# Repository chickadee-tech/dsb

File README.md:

# Chickadee Tech Dual Serial Breakout Polystack Mod #
This mod breakouts out two UARTs for any use. It includes 3.3v to 5v logic level shifting so ensure that all things connected are 5v tolerant.

## Documentation ##
See the [wiki](https://github.com/chickadee-tech/dsb/wiki) for documentation.

## Polystack ##
This **mod** board is part of the Polystack platform for modular microcontrol systems. More information on the platform can be found at [polystack.org](http://polystack.org).

## Support ##
If you need support with a board you own or have development questions please email support@chickadee.tech or check [chickadee.tech/support](https://chickadee.tech/support) for other ways to get support.

## Contributing ##
Please note that this project is released with a [Contributor Code of Conduct](CODE_OF_CONDUCT.md). By participating in this project you agree to abide by its terms.

### Setup ###
Components and footprints for PCB parts are not included in this repository. Instead, checkout the [chickadee-tech/kicad-libs](https://github.com/chickadee-tech/kicad-libs) repository in the same directory that this repository is checked out in. All part definitions should be relative so that they will load correctly.

### Pull requests ###
For fixes please submit a pull request to the original repository. After the pull request is merged, check the [Chickadee Tech Active Contributor Discount (ACD)](https://chickadee.tech/active-contributor) to see if you are eligible for a discount code to use on your next purchase.

### Derivatives ###
If developing your own version of the Dual Serial Breakout board please remove all Chickadee Tech trademarks and follow the [CC-BY license](LICENSE). While not required, please consider open sourcing your modifications so others can learn from your improvements. If you do email support@chickadee.tech and we may choose to add your project to the ACD.

You may also license the Polystack logo for free by emailing support@chickadee.tech. We'll ask for your gerbers to ensure the design complies with specifications laid out [here](https://github.com/chickadee-tech/polystack/wiki) and provide written permission to use the trademark after compliance has been demonstrated.

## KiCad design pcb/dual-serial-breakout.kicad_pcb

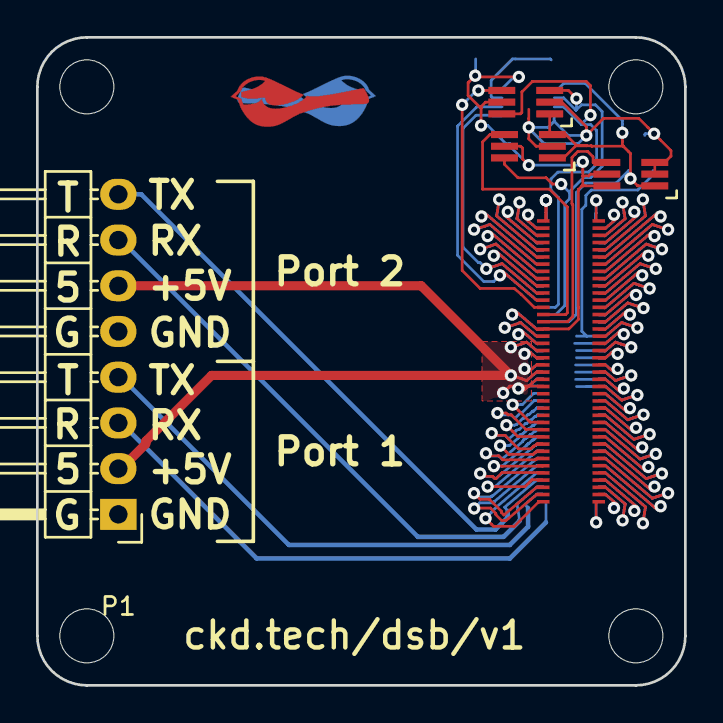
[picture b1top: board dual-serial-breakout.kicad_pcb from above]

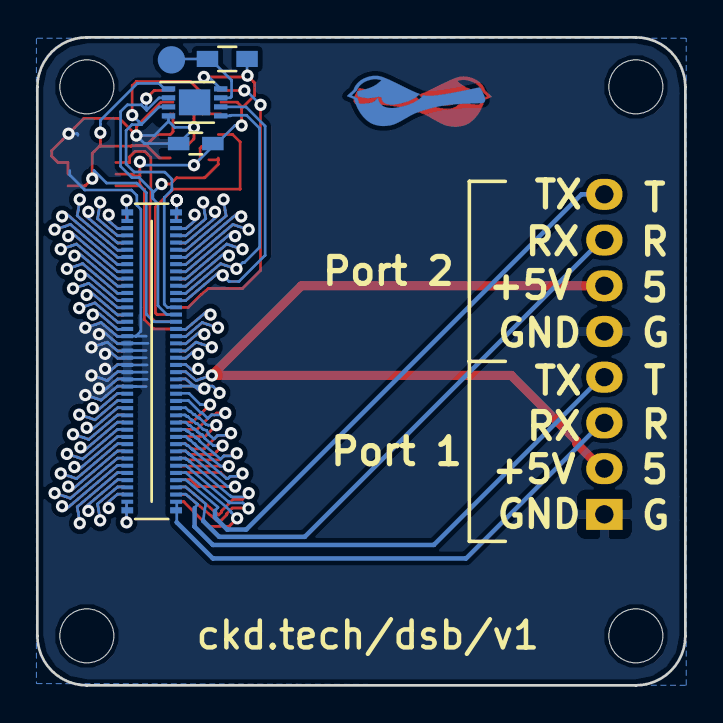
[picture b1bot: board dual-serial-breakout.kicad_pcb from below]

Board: 2 copper layers, 36.0 x 36.0 mm, 10 parts (5 on the bottom side), 72 nets.

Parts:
P1: CONN_01X08; Pin_Header_Angled_1x08
PORT_ANDOR1: SN74LVC1G0832; SC-70-6_Handsoldering
PORT_C1: 0.1uF; C_0603_HandSoldering
PORT_IC1: AT24CS02-MAHM; DFN-8-1EP_3x2mm_Pitch0.5mm
PORT_IN1: CKD_SANDWICH; DF40-80pin-Header
PORT_INV1: SN74LVC1G58; SC-70-6_Handsoldering
PORT_OUT1: CKD_SANDWICH; DF40-3-4mm-80pin-Receptacle
PORT_P1: CONN_01X01; Measurement_Point_Round-SMD-Pad_Small
PORT_R1: 10k; R_0603_HandSoldering
PORT_XOR1: SN74LVC1G58; SC-70-6_Handsoldering

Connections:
+5V: P1.2, P1.6, PORT_IN1.19, PORT_IN1.20, PORT_IN1.21, PORT_IN1.22, PORT_IN1.23, PORT_IN1.24, PORT_OUT1.19, PORT_OUT1.20, PORT_OUT1.21, PORT_OUT1.22, PORT_OUT1.23, PORT_OUT1.24
/ExpansionPort/3V3_0.3A_E: PORT_IN1.17, PORT_OUT1.17
/ExpansionPort/3V3_0.3A_LL: PORT_ANDOR1.5, PORT_C1.1, PORT_IC1.8, PORT_IN1.16, PORT_INV1.5, PORT_INV1.6, PORT_OUT1.16, PORT_R1.2, PORT_XOR1.5
/ExpansionPort/+BATT: PORT_IN1.18, PORT_OUT1.18
/ExpansionPort/ADC1: PORT_IN1.49, PORT_OUT1.49
/ExpansionPort/ADC2: PORT_IN1.50, PORT_OUT1.50
/ExpansionPort/GPIO1: PORT_IN1.5, PORT_OUT1.5
/ExpansionPort/GPIO2: PORT_IN1.6, PORT_OUT1.6
/ExpansionPort/GPIO3: PORT_IN1.7, PORT_OUT1.7
/ExpansionPort/GPIO4: PORT_IN1.8, PORT_OUT1.8
/ExpansionPort/HEIGHT_1: PORT_ANDOR1.1, PORT_IC1.1, PORT_IN1.15, PORT_INV1.1, PORT_XOR1.1, PORT_XOR1.3
/ExpansionPort/HEIGHT_2: PORT_ANDOR1.3, PORT_IC1.2, PORT_IN1.14, PORT_XOR1.6
/ExpansionPort/HEIGHT_4: PORT_ANDOR1.6, PORT_IC1.3, PORT_IN1.13
/ExpansionPort/NEW_HEIGHT_1: PORT_INV1.4, PORT_OUT1.15
/ExpansionPort/NEW_HEIGHT_2: PORT_OUT1.14, PORT_XOR1.4
/ExpansionPort/NEW_HEIGHT_4: PORT_ANDOR1.4, PORT_OUT1.13
/ExpansionPort/SDMMC1_CK: PORT_IN1.55, PORT_OUT1.55
/ExpansionPort/SDMMC1_CMD: PORT_IN1.56, PORT_OUT1.56
/ExpansionPort/SDMMC1_D0: PORT_IN1.51, PORT_OUT1.51
/ExpansionPort/SDMMC1_D1: PORT_IN1.52, PORT_OUT1.52
/ExpansionPort/SDMMC1_D2: PORT_IN1.53, PORT_OUT1.53
/ExpansionPort/SDMMC1_D3: PORT_IN1.54, PORT_OUT1.54
/ExpansionPort/SPI1_MISO: PORT_IN1.79, PORT_OUT1.79
/ExpansionPort/SPI1_MOSI: PORT_IN1.80, PORT_OUT1.80
/ExpansionPort/SPI1_NSS: PORT_IN1.77, PORT_OUT1.77
/ExpansionPort/SPI1_SCK: PORT_IN1.78, PORT_OUT1.78
/ExpansionPort/SPI2_MISO: PORT_IN1.75, PORT_OUT1.75
/ExpansionPort/SPI2_MOSI: PORT_IN1.76, PORT_OUT1.76
/ExpansionPort/SPI2_NSS: PORT_IN1.73, PORT_OUT1.73
/ExpansionPort/SPI2_SCK: PORT_IN1.74, PORT_OUT1.74
/ExpansionPort/SPI3_MISO: PORT_IN1.71, PORT_OUT1.71
/ExpansionPort/SPI3_MOSI: PORT_IN1.72, PORT_OUT1.72
/ExpansionPort/SPI3_NSS: PORT_IN1.69, PORT_OUT1.69
/ExpansionPort/SPI3_SCK: PORT_IN1.70, PORT_OUT1.70
/ExpansionPort/SPI4_MISO: PORT_IN1.67, PORT_OUT1.67
/ExpansionPort/SPI4_MOSI: PORT_IN1.68, PORT_OUT1.68
/ExpansionPort/SPI4_NSS: PORT_IN1.65, PORT_OUT1.65
/ExpansionPort/SPI4_SCK: PORT_IN1.66, PORT_OUT1.66
/ExpansionPort/TIM1: PORT_IN1.1, PORT_OUT1.1
/ExpansionPort/TIM2: PORT_IN1.2, PORT_OUT1.2
/ExpansionPort/TIM3: PORT_IN1.3, PORT_OUT1.3
/ExpansionPort/TIM4: PORT_IN1.4, PORT_OUT1.4
/ExpansionPort/TIMG1_CH1: PORT_IN1.41, PORT_OUT1.41
/ExpansionPort/TIMG1_CH2: PORT_IN1.42, PORT_OUT1.42
/ExpansionPort/TIMG1_CH3: PORT_IN1.43, PORT_OUT1.43
/ExpansionPort/TIMG1_CH4: PORT_IN1.44, PORT_OUT1.44
/ExpansionPort/TIMG2_CH1: PORT_IN1.45, PORT_OUT1.45
/ExpansionPort/TIMG2_CH2: PORT_IN1.46, PORT_OUT1.46
/ExpansionPort/TIMG2_CH3: PORT_IN1.47, PORT_OUT1.47
/ExpansionPort/TIMG2_CH4: PORT_IN1.48, PORT_OUT1.48
/ExpansionPort/UART1_RX: P1.3, PORT_IN1.40
/ExpansionPort/UART1_TX: P1.4, PORT_IN1.39
/ExpansionPort/UART2_RX: P1.7, PORT_IN1.38
/ExpansionPort/UART2_TX: P1.8, PORT_IN1.37
/ExpansionPort/UART3_RX: PORT_IN1.36, PORT_OUT1.40
/ExpansionPort/UART3_TX: PORT_IN1.35, PORT_OUT1.39
/ExpansionPort/UART4_RX: PORT_IN1.34, PORT_OUT1.38
/ExpansionPort/UART4_TX: PORT_IN1.33, PORT_OUT1.37
/ExpansionPort/UART5_RX: PORT_IN1.32, PORT_OUT1.36
/ExpansionPort/UART5_TX: PORT_IN1.31, PORT_OUT1.35
/ExpansionPort/UART6_RX: PORT_IN1.30, PORT_OUT1.34
/ExpansionPort/UART6_TX: PORT_IN1.29, PORT_OUT1.33
/ExpansionPort/UART7_RX: PORT_IN1.28, PORT_OUT1.32
/ExpansionPort/UART7_TX: PORT_IN1.27, PORT_OUT1.31
/ExpansionPort/UART8_RX: PORT_IN1.26, PORT_OUT1.30
/ExpansionPort/UART8_TX: PORT_IN1.25, PORT_OUT1.29
/ExpansionPort/si2c_SCL: PORT_IC1.6, PORT_IN1.12, PORT_OUT1.12
/ExpansionPort/si2c_SDA: PORT_IC1.5, PORT_IN1.11, PORT_OUT1.11
/ExpansionPort/xi2c1_SCL: PORT_IN1.10, PORT_OUT1.10
/ExpansionPort/xi2c1_SDA: PORT_IN1.9, PORT_OUT1.9
GNDPWR: P1.1, P1.5, PORT_ANDOR1.2, PORT_C1.2, PORT_IC1.4, PORT_IN1.57, PORT_IN1.58, PORT_IN1.59, PORT_IN1.60, PORT_IN1.61, PORT_IN1.62, PORT_IN1.63, PORT_IN1.64, PORT_INV1.2, PORT_INV1.3, PORT_OUT1.57, PORT_OUT1.58, PORT_OUT1.59, PORT_OUT1.60, PORT_OUT1.61, PORT_OUT1.62, PORT_OUT1.63, PORT_OUT1.64, PORT_XOR1.2
unnamed: PORT_IC1.7, PORT_P1.1, PORT_R1.1

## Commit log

2015-11-11 Fix up dual serial breakout DRC.
2016-04-07 Add logic level conversion.
2016-04-13 Rebrand everything to Polystack and increment versions.
2016-04-16 Final gerbers for test manufacturing run.
2016-06-07 Update polystack logo to bold variant and bump version number.
2016-07-07 Add license information to many files. PCB design files are CC-BY and code is MIT license.
2016-07-07 Add back .gitignore after repo split.
2016-07-07 Convert to relative component and footprint paths.
2016-07-09 Dual serial breakout v1.
